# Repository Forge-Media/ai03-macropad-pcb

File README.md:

# ai03 Inspired Macropad PCB

My attempt at learning and implementing ai03's guide to pcb design for keyboards. The aim of this project is to design and manufacture a simple 3by3 MX style macropad pcb, which actually works. The pcb can then be manufactured and either assembled by hand or by the manufacturer if they provide assembly service.

## Project requirements:

- 9 1U MX-Hotswap switches
- USB-C support
- Atmega32u4 support (MU QFN-44 version)
- Per-key RGB LED (9 LEDs)
- RGB Underglow (4 LEDs)
- ESD and Reverse Bias protection (Fused VCC and +5v)
- QMK support
- VIA support (TBD)

## CAD

KiCad 5.1.9 is used for the pcb design, based on [ai03's guide](https://wiki.ai03.com/books/pcb-design).

**Required KiCad libraries:**

- [ai03's KiCad Type-C library](https://github.com/ai03-2725/Type-C.pretty) (USB-C 2.0 connector)
- [ai03's hybrid footprints](https://github.com/ai03-2725/MX_Alps_Hybrid/tree/master/MX_Only.pretty) (Kailh Hotswap footprints)
- [ai03's random components](https://github.com/ai03-2725/random-keyboard-parts.pretty) (Reset button footprint)
- [ebastler's kicad components](https://github.com/ebastler/kicad-keyboard-parts.pretty) (RGB LEDs footprints and 3D models)

**Optional KiCad libraries:**

- [KiCad included switches](https://kicad.github.io/footprints/Button_Switch_Keyboard) (Solder MX footprints) (Unless 5.1.9 or later)
- [Perigoso's KiCad Keyboard libraries](https://github.com/perigoso/keyswitch-kicad-library) (Alternative MX footprints)
- (TBD)

Autocad, Rhino and Fusion 360 are used for the case design.

## References:

- [ai03's - pcb guide](https://wiki.ai03.com/books/pcb-design)
- [ai03's KiCad library list](https://wiki.ai03.com/books/pcb-design/page/list-of-kicad-keyboard-parts-libraries)
- [33C Discord](https://discord.gg/6fHK4uk)
- [Keyboard Atelier Discord](https://discord.gg/b7vwhHS)
- [QMK Docs](https://beta.docs.qmk.fm/developing-qmk/c-development/compatible_microcontrollers)
- [Hadi's - PCB design series](https://www.youtube.com/channel/UCpWGAJr2AU7LPUwVYbBQZRg/playlists) (Incomplete!)
- [KoBuss' - How we designed a mechanicial keyboard pcb](https://www.youtube.com/watch?v=ezk02GJ9iMs)
- [MrKeebs' - PCB from Scratch with Gondo series](https://www.youtube.com/watch?v=Nk0egpDFqRA)
- [FJ Laboratories Blog](https://www.fjlaboratories.com/)
- (TBD)

## License

MIT License

Copyright (c) 2021 ForgeMedia (Jeremy Paton)

Permission is hereby granted, free of charge, to any person obtaining a copy of this hardware, software, and associated documentation files (the "Product"), to deal in the Product without restriction, including without limitation the rights to use, copy, modify, merge, publish, distribute, sublicense, and/or sell copies of the Product, and to permit persons to whom the Product is furnished to do so, subject to the following conditions:

The above copyright notice and this permission notice shall be included in all copies or substantial portions of the Product.

THE PRODUCT IS PROVIDED "AS IS", WITHOUT WARRANTY OF ANY KIND, EXPRESS OR IMPLIED, INCLUDING BUT NOT LIMITED TO THE WARRANTIES OF MERCHANTABILITY, FITNESS FOR A PARTICULAR PURPOSE AND NONINFRINGEMENT. IN NO EVENT SHALL THE AUTHORS OR COPYRIGHT HOLDERS BE LIABLE FOR ANY CLAIM, DAMAGES OR OTHER LIABILITY, WHETHER IN AN ACTION OF CONTRACT, TORT OR OTHERWISE, ARISING FROM, OUT OF OR IN CONNECTION WITH THE PRODUCT OR THE USE OR OTHER DEALINGS IN THE PRODUCT.

## For the Keyboard Community

You can produce and sell this keyboard design. ForgeMedia (Jeremy Paton) is not liable. Creator attribution is required however, no use of the creator's or 3rd party branding may be utilised in a derivative. This includes logos and brand names.

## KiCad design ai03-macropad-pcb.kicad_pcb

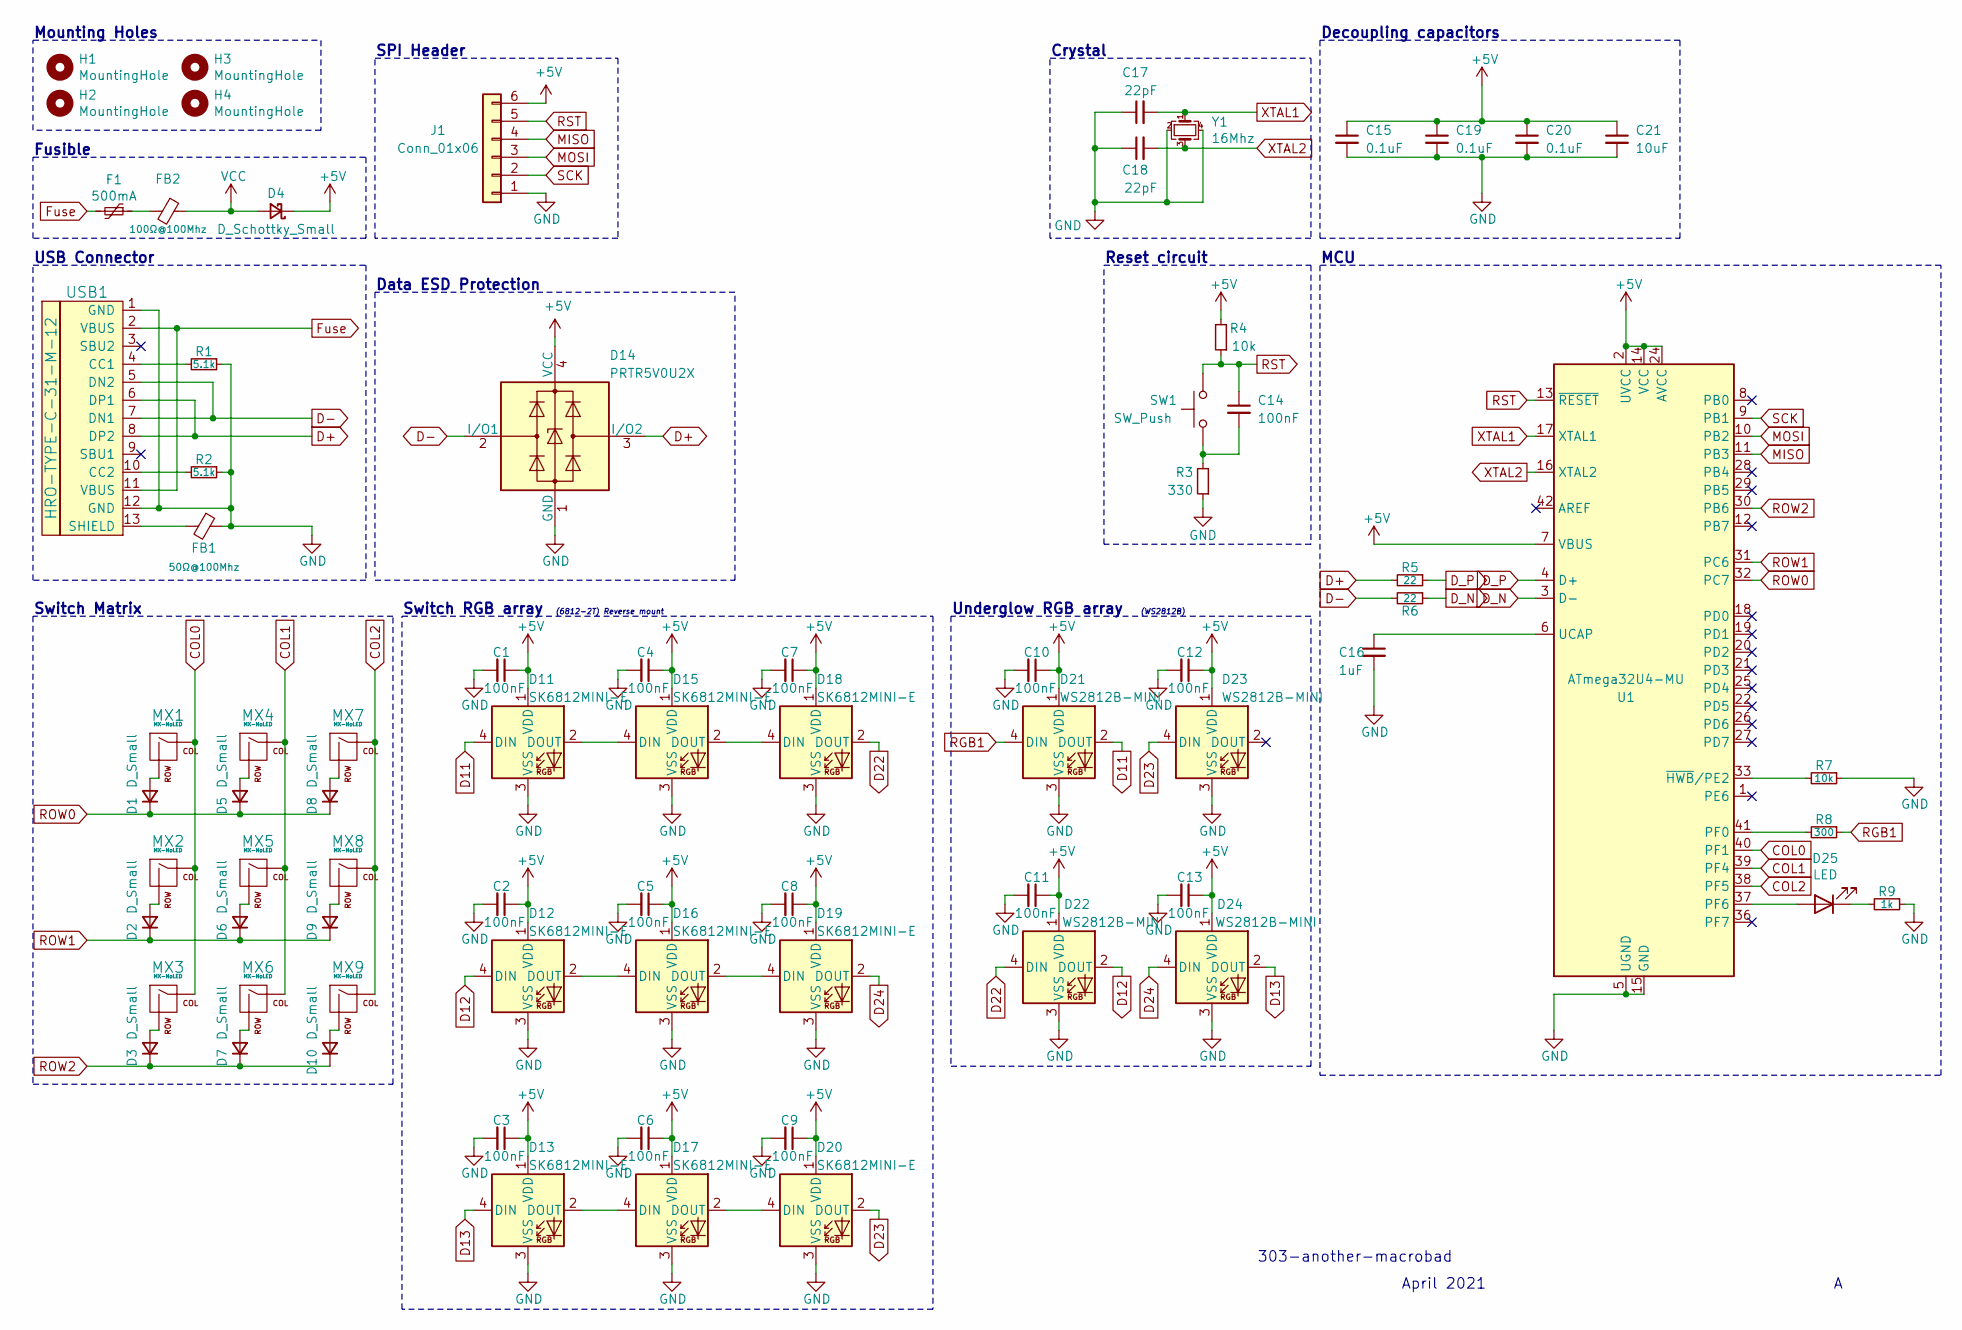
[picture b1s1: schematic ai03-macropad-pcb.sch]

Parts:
C1, C2, C3, C4, C5, C6, C7, C8, C9, C10, C11, C12, C13, C14: 100nF; C_0603_1608Metric
C15, C19, C20: 0.1uF; C_0603_1608Metric
C16: 1uF; C_0603_1608Metric
C17, C18: 22pF; C_0603_1608Metric
C21: 10uF; C_0603_1608Metric
D1, D2, D3, D5, D6, D7, D8, D9, D10: D_Small; D_SOD-123
D4: D_Schottky_Small; D_SOD-123
D11, D12, D13, D15, D16, D17, D18, D19, D20: SK6812MINI-E; MX_SK6812MINI-E
D14: PRTR5V0U2X; SOT-143
D21, D22, D23, D24: WS2812B-MINI; LED_SK6812MINI_PLCC4_3.5x3.5mm_P1.75mm
D25: LED; LED_0603_1608Metric
F1: 500mA; Fuse_0805_2012Metric
FB1: 50Ω@100Mhz; Fuse_0603_1608Metric
FB2: 100Ω@100Mhz; Fuse_0805_2012Metric
H1, H2, H3, H4: MountingHole; MountingHole_3.2mm_M3_DIN965_Pad
J1: Conn_01x06; JST_SHL_SM06B-SHLS-TF_1x06-1MP_P1.00mm_Horizontal
MX1, MX2, MX3, MX4, MX5, MX6, MX7, MX8, MX9: MX-NoLED; MXOnly-1U-Hotswap-Antishear
R1, R2: 5.1k; R_0603_1608Metric
R3: 330; R_0603_1608Metric
R4, R7: 10k; R_0603_1608Metric
R5, R6: 22; R_0603_1608Metric
R8: 300; R_0603_1608Metric
R9: 1k; R_0603_1608Metric
SW1: SW_Push; SW_SPST_CK_KXT3
U1: ATmega32U4-MU; QFN-44-1EP_7x7mm_P0.5mm_EP5.2x5.2mm
USB1: HRO-TYPE-C-31-M-12; HRO-TYPE-C-31-M-12-Assembly
Y1: 16Mhz; Crystal_SMD_3225-4Pin_3.2x2.5mm

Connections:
+5V: C1.1, C2.1, C3.1, C4.1, C5.1, C6.1, C7.1, C8.1, C9.1, C10.1, C11.1, C12.1, C13.1, C15.1, C19.1, C20.1, C21.1, D4.1 (K), D11.1 (VDD), D12.1 (VDD), D13.1 (VDD), D14.4 (VCC), D15.1 (VDD), D16.1 (VDD), D17.1 (VDD), D18.1 (VDD), D19.1 (VDD), D20.1 (VDD), D21.1 (VDD), D22.1 (VDD), D23.1 (VDD), D24.1 (VDD), J1.6, R4.2, U1.2 (UVCC), U1.7 (VBUS), U1.14 (VCC), U1.24 (AVCC), U1.34 (VCC), U1.44 (AVCC); also elsewhere on the board
COL0: MX1.1 (COL), MX2.1 (COL), MX3.1 (COL), U1.40 (PF1)
COL1: MX4.1 (COL), MX5.1 (COL), MX6.1 (COL), U1.39 (PF4)
COL2: MX7.1 (COL), MX8.1 (COL), MX9.1 (COL), U1.38 (PF5)
D11: D11.4 (DIN), D21.2 (DOUT)
D12: D12.4 (DIN), D22.2 (DOUT)
D13: D13.4 (DIN), D24.2 (DOUT)
D22: D18.2 (DOUT), D22.4 (DIN)
D23: D20.2 (DOUT), D23.4 (DIN)
D24: D19.2 (DOUT), D24.4 (DIN)
D+: D14.3 (I/O2), R5.2, USB1.6 (DP1), USB1.8 (DP2)
D-: D14.2 (I/O1), R6.2, USB1.5 (DN2), USB1.7 (DN1)
D_N: R6.1, U1.3 (D-)
D_P: R5.1, U1.4 (D+)
Fuse: F1.2, USB1.2 (VBUS), USB1.11 (VBUS)
GND: C1.2, C2.2, C3.2, C4.2, C5.2, C6.2, C7.2, C8.2, C9.2, C10.2, C11.2, C12.2, C13.2, C15.2, C16.2, C17.1, C18.1, C19.2, C20.2, C21.2, D11.3 (VSS), D12.3 (VSS), D13.3 (VSS), D14.1 (GND), D15.3 (VSS), D16.3 (VSS), D17.3 (VSS), D18.3 (VSS), D19.3 (VSS), D20.3 (VSS), D21.3 (VSS), D22.3 (VSS), D23.3 (VSS), D24.3 (VSS), FB1.1, J1.1, R1.1, R2.1, R3.1, R7.1, R9.1, U1.5 (UGND), U1.15 (GND), U1.23 (GND), U1.35 (GND), U1.43 (GND), U1.45 (GND), USB1.1 (GND), USB1.12 (GND), Y1.2, Y1.4; also elsewhere on the board
MISO: J1.4, U1.11 (PB3); also elsewhere on the board
MOSI: J1.3, U1.10 (PB2); also elsewhere on the board
unnamed: C14.2, R3.2, SW1.1
unnamed: C16.1, U1.6 (UCAP)
unnamed: D1.2 (A), MX1.2 (ROW)
unnamed: D2.2 (A), MX2.2 (ROW)
unnamed: D3.2 (A), MX3.2 (ROW)
unnamed: D5.2 (A), MX4.2 (ROW)
unnamed: D6.2 (A), MX5.2 (ROW)
unnamed: D7.2 (A), MX6.2 (ROW)
unnamed: D8.2 (A), MX7.2 (ROW)
unnamed: D9.2 (A), MX8.2 (ROW)
unnamed: D10.2 (A), MX9.2 (ROW)
unnamed: D11.2 (DOUT), D15.4 (DIN)
unnamed: D12.2 (DOUT), D16.4 (DIN)
unnamed: D13.2 (DOUT), D17.4 (DIN)
unnamed: D15.2 (DOUT), D18.4 (DIN)
unnamed: D16.2 (DOUT), D19.4 (DIN)
unnamed: D17.2 (DOUT), D20.4 (DIN)
unnamed: D25.1 (K), R9.2
unnamed: D25.2 (A), U1.37 (PF6)
unnamed: F1.1, FB2.2
unnamed: FB1.2, USB1.13 (SHIELD)
unnamed: R1.2, USB1.4 (CC1)
unnamed: R2.2, USB1.10 (CC2)
unnamed: R7.2, U1.33 (~HWB~/PE2)
unnamed: R8.2, U1.41 (PF0)
RGB1: D21.4 (DIN), R8.1
ROW0: D1.1 (K), D5.1 (K), D8.1 (K), U1.32 (PC7)
ROW1: D2.1 (K), D6.1 (K), D9.1 (K), U1.31 (PC6)
ROW2: D3.1 (K), D7.1 (K), D10.1 (K), U1.30 (PB6)
RST: C14.1, J1.5, R4.1, SW1.2, U1.13 (~RESET); also elsewhere on the board
SCK: J1.2, U1.9 (PB1); also elsewhere on the board
VCC: D4.2 (A), FB2.1
XTAL1: C17.2, U1.17 (XTAL1), Y1.1
XTAL2: C18.2, U1.16 (XTAL2), Y1.3

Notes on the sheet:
Data ESD Protection
USB Connector
Fusible
SPI Header
MCU
Reset circuit
Decoupling capacitors
Mounting Holes
Switch Matrix
Switch RGB array
Underglow RGB array
(6812-2T) Reverse mount
(WS2812B)
Crystal
303-another-macrobad
April 2021

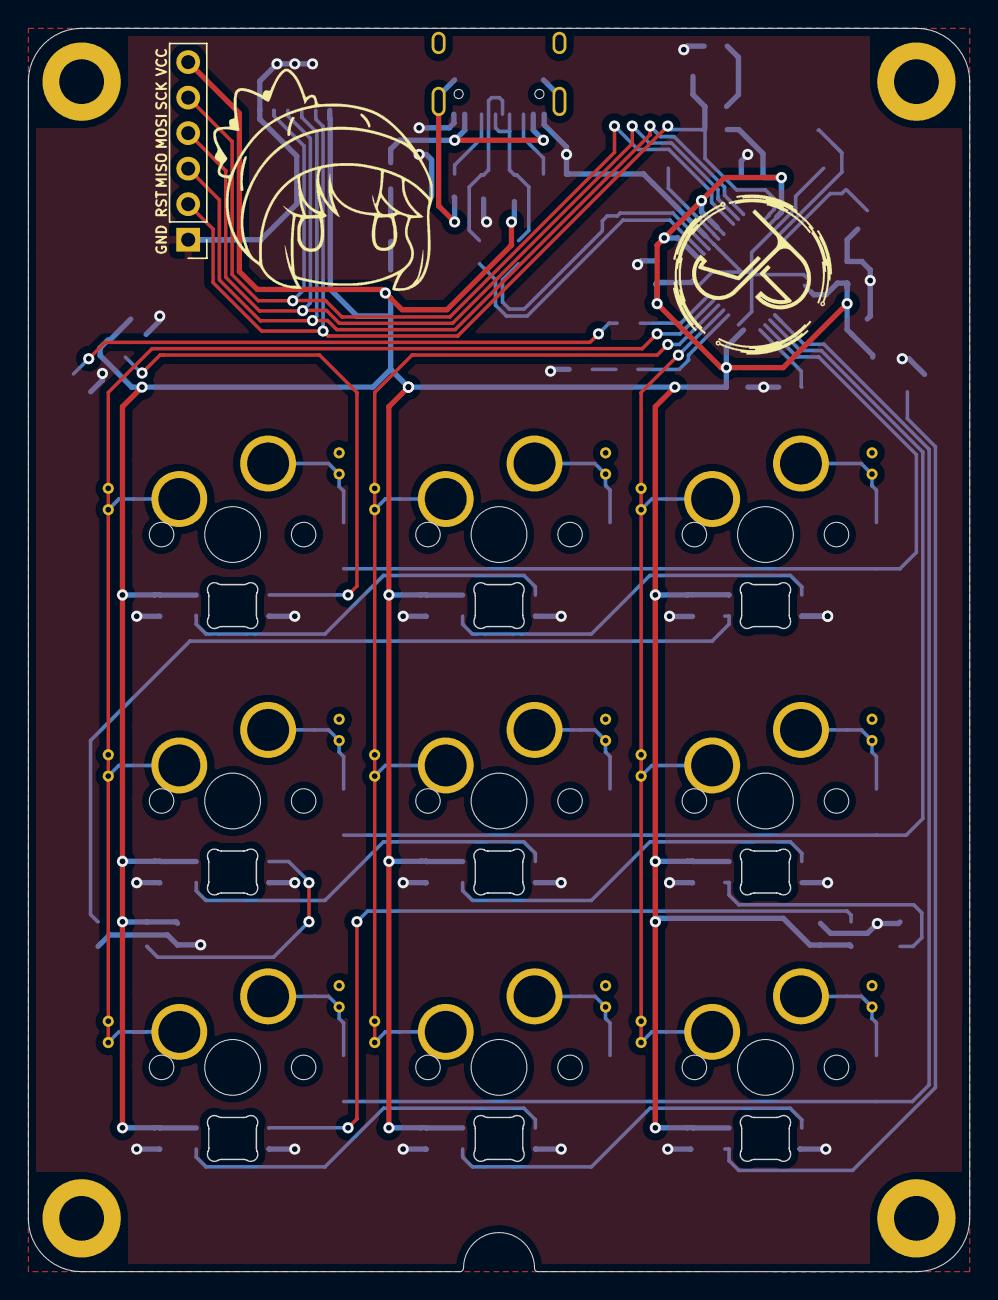
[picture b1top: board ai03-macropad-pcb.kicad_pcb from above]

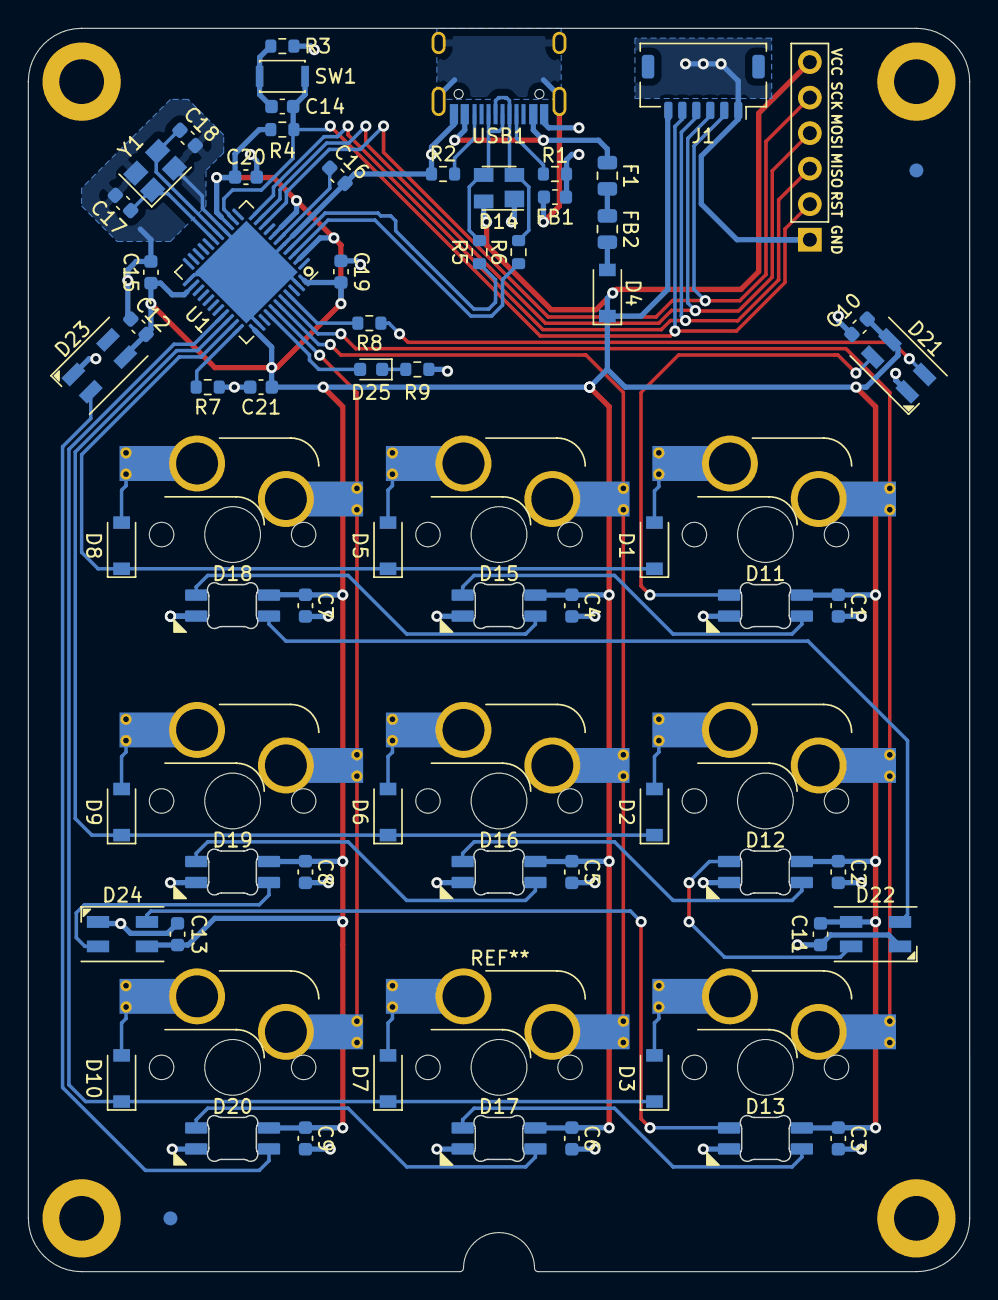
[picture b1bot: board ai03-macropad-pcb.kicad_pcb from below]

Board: 2 copper layers, 67.3 x 88.9 mm, 77 parts (54 on the bottom side), 52 nets.

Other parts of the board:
J2: ICSP; ICSP-Header

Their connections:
+5V: J2.6; also elsewhere on the board
GND: J2.1; also elsewhere on the board
MISO: J2.3; also elsewhere on the board
MOSI: J2.4; also elsewhere on the board
RST: J2.2; also elsewhere on the board
SCK: J2.5; also elsewhere on the board

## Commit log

2021-04-09 KiCad init
2021-04-09 Project requirements and references
2021-04-09 KiCad Library added as sub-modules
2021-04-09 Added project libraries to KiCad
2021-04-09 MCU boilerplate schematic
2021-04-10 USB-C and ESD schematic
2021-04-11 Switch matrix and RGB array
2021-04-11 Footprints and schematic fixes
2021-04-11 Schematic improvements and added libraries
2021-04-11 Library alterations
2021-04-13 Routing for switches and RGBs
2021-04-14 Routing of MCU, USB and BUS Lanes
2021-04-22 RevA Routing complete
2021-04-22 RevA DRC check
2021-04-22 Gerbers pre-prod
